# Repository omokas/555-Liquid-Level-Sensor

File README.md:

# 555 Liquid Level Sensor

This project is a level sensor PCB utilising a 555 timer and a few external components.

It was developed during my internship with ΔΕΥΑΧ (Public Company of Water Supply and Sewage of Chania) to be tested in water storage facilities

# PCB 

## Credits
Orestis Mokas - PCB Design

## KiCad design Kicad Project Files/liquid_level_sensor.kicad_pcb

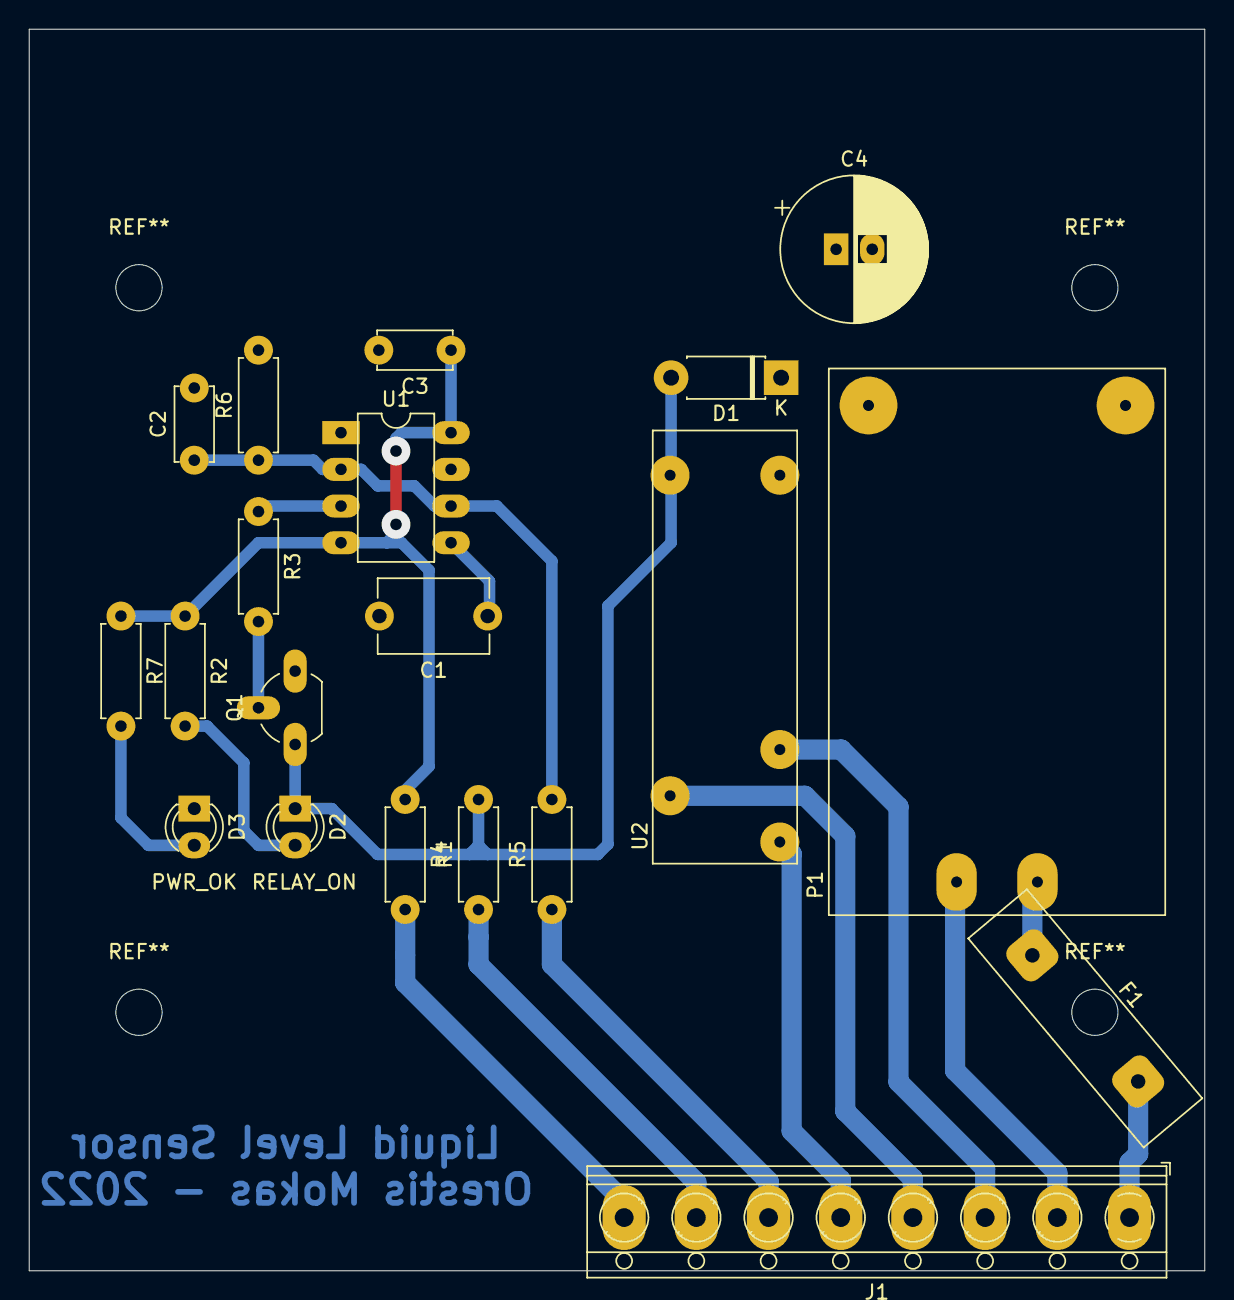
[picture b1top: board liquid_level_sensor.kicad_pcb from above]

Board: 2 copper layers, 81.4 x 86.0 mm, 20 parts (0 on the bottom side), 18 nets.

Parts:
C1: 0.1uF; C_Disc_D7.5mm_W5.0mm_P7.50mm
C2, C3: 0.1uF; C_Disc_D5.0mm_W2.5mm_P5.00mm
C4: 100uF; CP_Radial_D10.0mm_P2.50mm
D1: 1N4007; D_DO-41_SOD81_P7.62mm_Horizontal
D2, D3: LED; LED_D3.0mm
F1: Fuse; Fuse_Littelfuse-LVR100
J1: Conn_01x08; TerminalBlock_RND_205-00018_1x08_P5.00mm_Horizontal
P1: AC_PSU; HiLink_PSU
Q1: BC337; TO-92_Wide
R1: 33K; R_Axial_DIN0207_L6.3mm_D2.5mm_P7.62mm_Horizontal
R2, R3, R4: 2K2; R_Axial_DIN0207_L6.3mm_D2.5mm_P7.62mm_Horizontal
R5, R7: 10K; R_Axial_DIN0207_L6.3mm_D2.5mm_P7.62mm_Horizontal
R6: 1M; R_Axial_DIN0207_L6.3mm_D2.5mm_P7.62mm_Horizontal
U1: LM555xN; DIP-8_W7.62mm
U2: RM96P

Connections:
AC_F_L: F1.1, P1.2
AC_L: F1.2, J1.1
AC_N: J1.2, P1.1
GND: C1.2, C2.2, C3.2, C4.2, D3.1, P1.3, Q1.3, R6.2, U1.1
J1: C2.1, R5.2, R6.1, U1.2, U1.6
J2: D1.2, D2.1, Q1.1, R1.2, U2.2
LEVEL_1: J1.8, R4.2
LEVEL_2: J1.7, R1.1
LEVEL_3: J1.6, R5.1
unnamed: C1.1, U1.5
unnamed: D2.2, R2.2
unnamed: D3.2, R7.2
unnamed: Q1.2, R3.2
unnamed: R3.1, U1.3
REL_COM: J1.4, U2.4
REL_NC: J1.3, U2.3
REL_NO: J1.5, U2.5
VCC: C3.1, C4.1, D1.1, P1.4, R2.1, R4.1, R7.1, U1.4, U1.8, U2.1

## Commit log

2025-09-26 Add files
2025-09-26 Create 1
2025-09-26 Add KiCad project files
2025-09-26 Correct schematic
2025-09-26 Update README.md
    Add PCB photo
